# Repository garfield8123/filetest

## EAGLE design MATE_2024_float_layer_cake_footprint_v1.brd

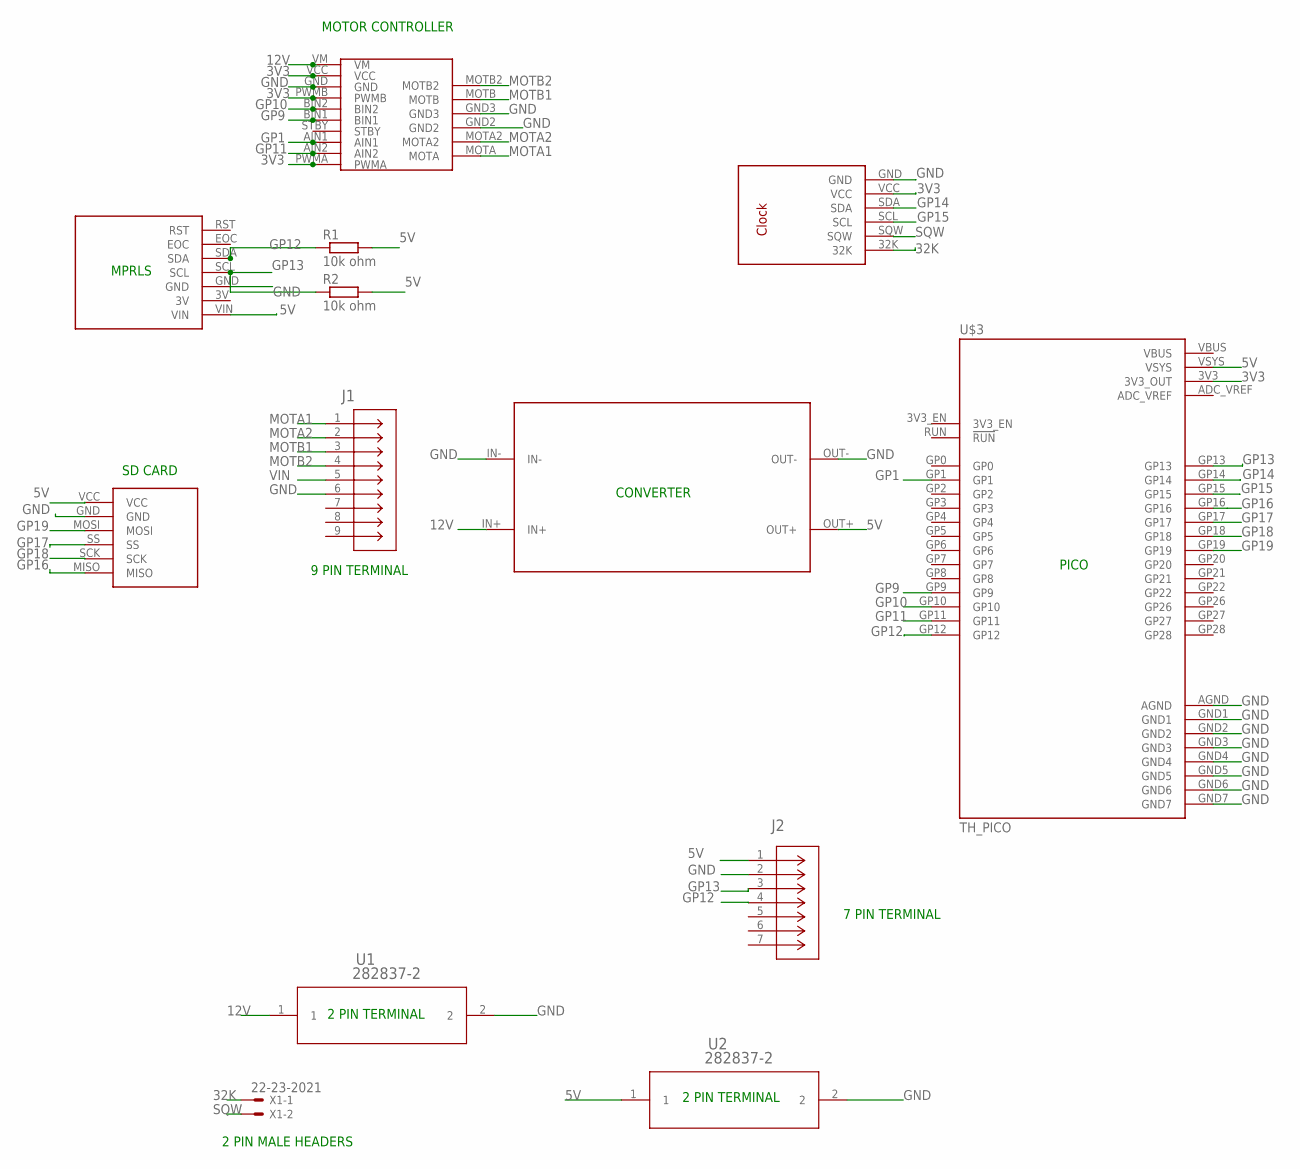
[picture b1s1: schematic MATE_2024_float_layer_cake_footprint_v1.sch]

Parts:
J1: 282837-9; CONN9_282837-9_TEC
J2: 282837-7; 282837-7_TEC
PRESSURE: PRESSURE
R1, R2: 10k ohm; 0204/7
U1, U2: 282837-2; 282837-2_TYC
U$1: CONVERTER
U$2: STEPPERMOTOR; STEPPERV2
U$3: TH_PICO
U$5: MICROSDCARD
U$6: CLOCKMODULE
X1: 22-23-2021

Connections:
3V3: U$2.PWMA, U$2.PWMB, U$2.VCC, U$3.3V3 (3V3_OUT), U$6.VCC
5V: J2.1, PRESSURE.VIN, R1.2, R2.2, U2.1, U$1.OUT+, U$3.VSYS, U$5.VCC
12V: U1.1, U$1.IN+, U$2.VM
32K: U$6.32K, X1.1
ADC_VREF: U$3.ADC_VREF
GND: J1.6, J2.2, PRESSURE.GND, U1.2, U2.2, U$1.IN-, U$1.OUT-, U$2.GND, U$2.GND2, U$2.GND3, U$3.AGND, U$3.GND1, U$3.GND2, U$3.GND3, U$3.GND4, U$3.GND5, U$3.GND6, U$3.GND7, U$5.GND, U$6.GND
GP1: U$2.AIN1, U$3.GP1
GP9: U$2.BIN1, U$3.GP9
GP10: U$2.BIN2, U$3.GP10
GP11: U$2.AIN2, U$3.GP11
GP12: J2.4, PRESSURE.SDA, R1.1, U$3.GP12
GP13: J2.3, PRESSURE.SCL, R2.1, U$3.GP13
GP14: U$3.GP14, U$6.SDA
GP15: U$3.GP15, U$6.SCL
GP16: U$3.GP16, U$5.MISO
GP17: U$3.GP17, U$5.SS
GP18: U$3.GP18, U$5.SCK
GP19: U$3.GP19, U$5.MOSI
MOTA1: J1.1, U$2.MOTA
MOTA2: J1.2, U$2.MOTA2
MOTB1: J1.3, U$2.MOTB
MOTB2: J1.4, U$2.MOTB2
SQW: U$6.SQW, X1.2
VBUS: U$3.VBUS
VIN: J1.5

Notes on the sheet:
CONVERTER
SD CARD
MPRLS
PICO
2 PIN TERMINAL
7 PIN TERMINAL
9 PIN TERMINAL
MOTOR CONTROLLER
2 PIN MALE HEADERS

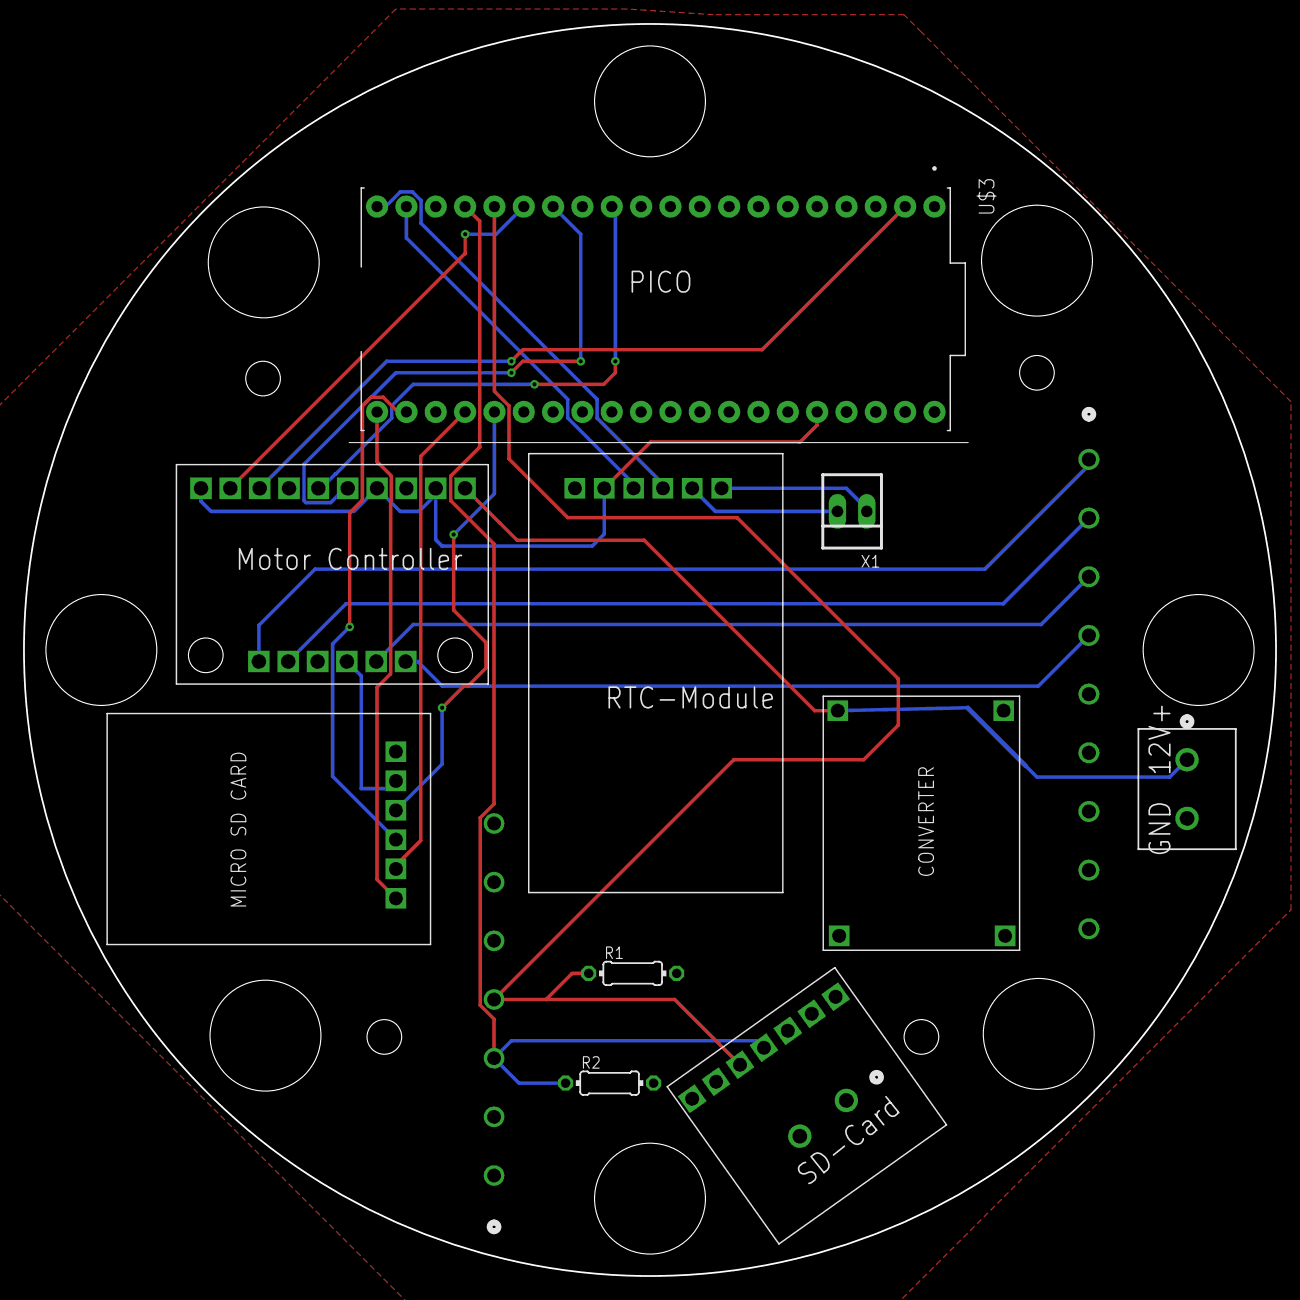
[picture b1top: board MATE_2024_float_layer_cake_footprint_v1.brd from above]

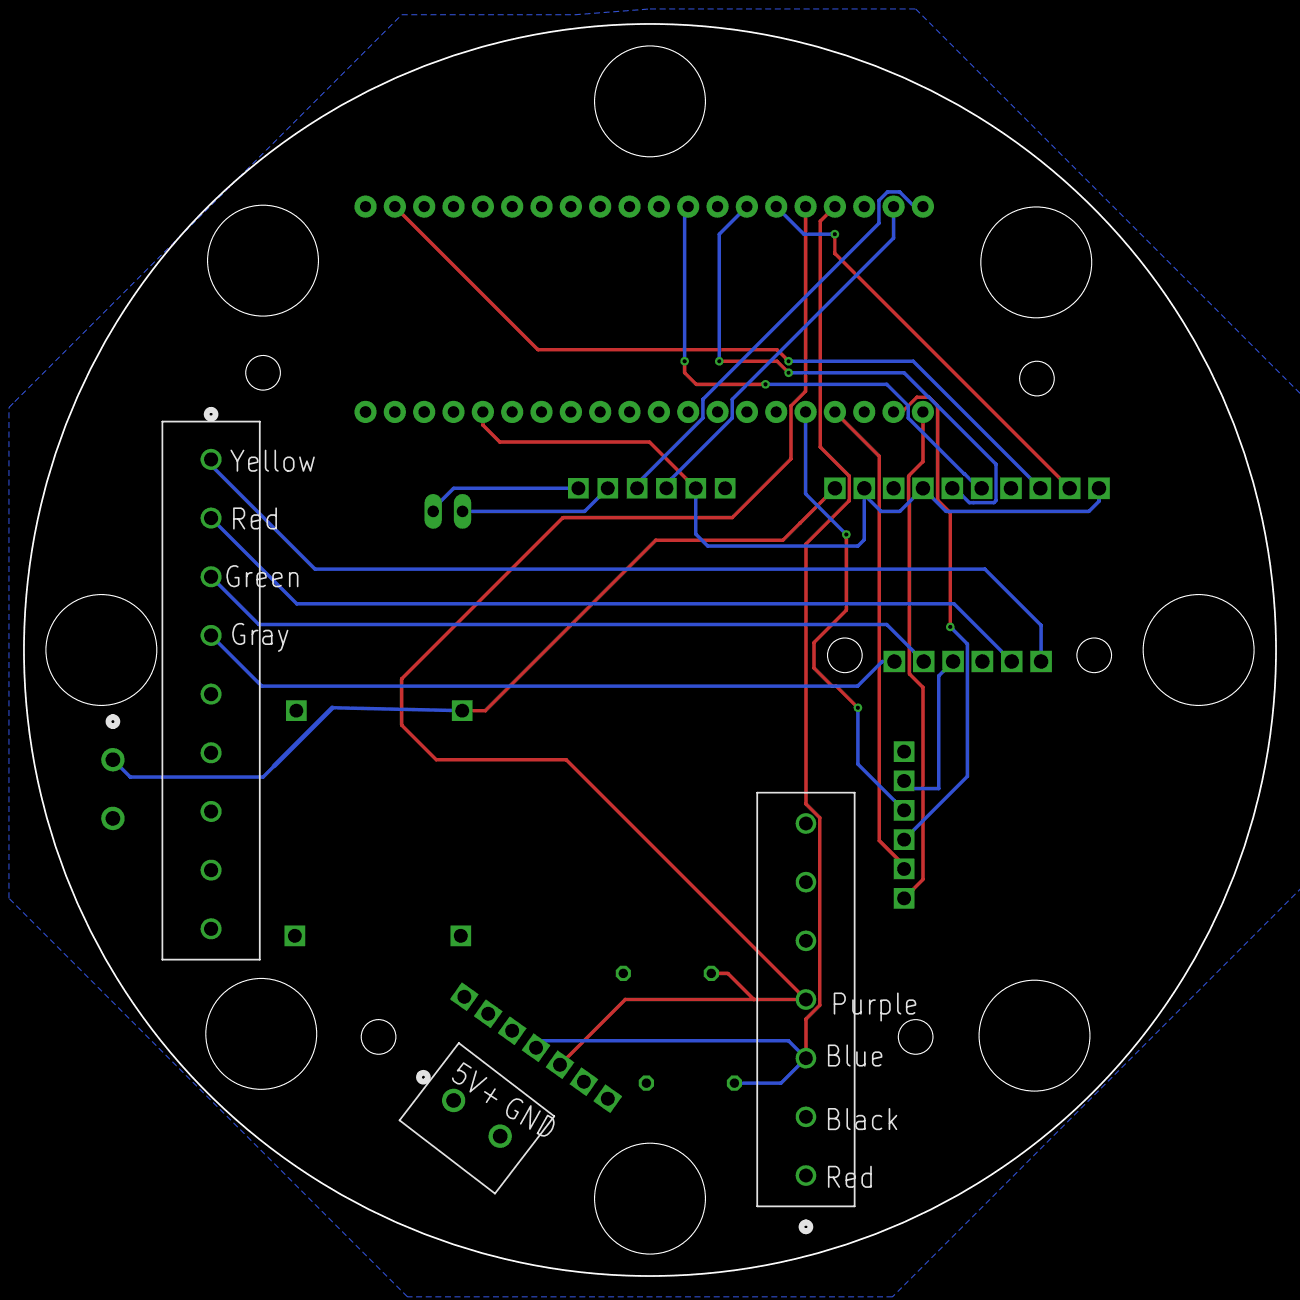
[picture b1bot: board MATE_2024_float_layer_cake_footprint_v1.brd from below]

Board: 2 copper layers, 108.4 x 108.4 mm, 13 parts (3 on the bottom side), 22 nets.

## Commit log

2024-05-24 upload

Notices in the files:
parts and their libraries:
COPYRIGHT: Copyright (C) 2024 Ultra Librarian. All rights reserved.
